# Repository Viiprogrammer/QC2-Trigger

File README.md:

# QC2-Trigger
QC2-Trigger 5V 9 V 12V

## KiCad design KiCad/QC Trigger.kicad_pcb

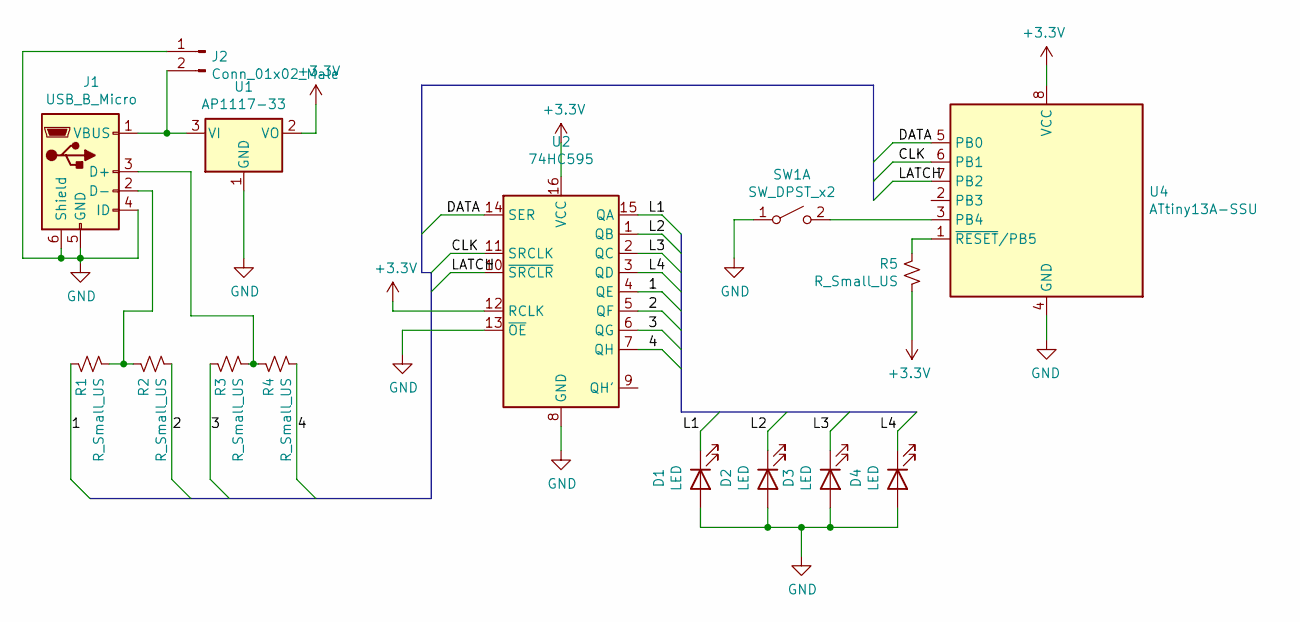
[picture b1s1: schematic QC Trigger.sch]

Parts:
D1, D2, D3, D4: LED; LED_1206_3216Metric
J1: USB_B_Micro; USB_Micro-B_Amphenol_10104110_Horizontal
J2: Conn_01x02_Male; PinHeader_1x02_P2.54mm_Vertical
R1, R2, R3, R4, R5: R_Small_US; R_1206_3216Metric
SW1: SW_DPST_x2; SW_SPST_CK_RS282G05A3
U1: AP1117-33; SOT-223-3_TabPin2
U2: 74HC595; SOIC-16_3.9x9.9mm_P1.27mm
U4: ATtiny13A-SSU; SOIC-8_3.9x4.9mm_P1.27mm

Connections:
+3V3: R5.2, U1.2 (VO), U2.12 (RCLK), U2.16 (VCC), U4.8 (VCC)
/1: R1.1, U2.4 (QE)
/2: R2.2, U2.5 (QF)
/3: R3.1, U2.6 (QG)
/4: R4.2, U2.7 (QH)
/CLK: U2.11 (SRCLK), U4.6 (PB1)
/DATA: U2.14 (SER), U4.5 (PB0)
/L1: D1.1 (K), U2.15 (QA)
/L2: D2.1 (K), U2.1 (QB)
/L3: D3.1 (K), U2.2 (QC)
/L4: D4.1 (K), U2.3 (QD)
/LATCH: U2.10 (~SRCLR), U4.7 (PB2)
GND: D1.2 (A), D2.2 (A), D3.2 (A), D4.2 (A), J1.4 (ID), J1.5 (GND), J1.6 (Shield), J2.1, SW1.1 (A), U1.1 (GND), U2.8 (GND), U2.13 (~OE), U4.4 (GND)
unnamed: J1.1 (VBUS), J2.2, U1.3 (VI)
unnamed: J1.2 (D-), R1.2, R2.1
unnamed: J1.3 (D+), R3.2, R4.1
unnamed: R5.1, U4.1 (~RESET~/PB5)
unnamed: SW1.2 (B), U4.3 (PB4)

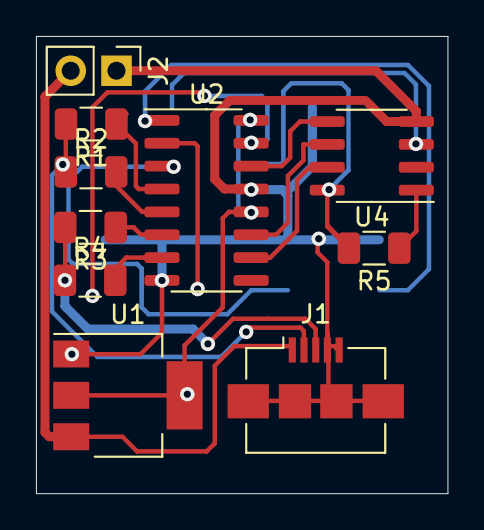
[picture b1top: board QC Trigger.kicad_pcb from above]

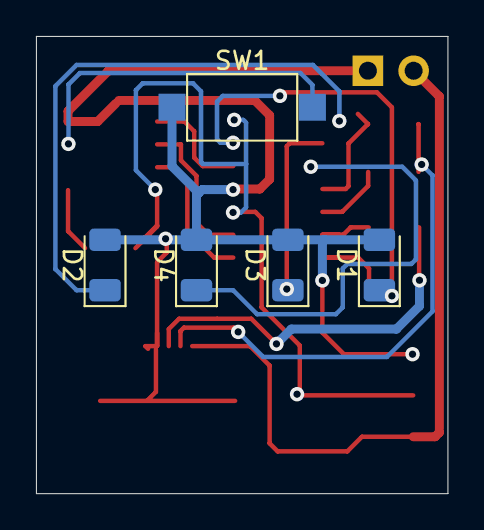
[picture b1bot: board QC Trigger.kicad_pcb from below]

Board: 2 copper layers, 22.9 x 25.4 mm, 15 parts (5 on the bottom side), 18 nets.

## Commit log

2019-07-12 Add files
2020-01-26 backup
2020-09-05 Add KiCAD and Update 74hc595 lib
